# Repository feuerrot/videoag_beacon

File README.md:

# VideoAG Projekt: Beacon

Hardware ist an unbekannten Orten. Aber für die Aufnahme von Vorlesungen wüssten wir gerne, welche Hardware sich wo befindet. Die Lösung: Ein Beacon.
Auf der Basis eines nRF24L01+ und eines AVR wird so ein preiswertes und stromsparendes Stück Hardware implementiert, die sich jeweils am Equipment befindet und in regelmäßigen Intervallen eine eindeutige ID aussendet. Diese ID wird dann von einem dauerhaft lauschenden Empfänger verarbeitet.

## Projektstatus
Es existiert eine weitgehend stabile und laut Datenblätter stromsparende Idee für die Beacons. Platinen wurden designed und geätzt.

## Todo
* Platinen bestücken
* Firmware entwickeln
* Hardware testen
* Hardware für die Station designen

## Schaltplan und Layout

### Schaltplan

### Layout

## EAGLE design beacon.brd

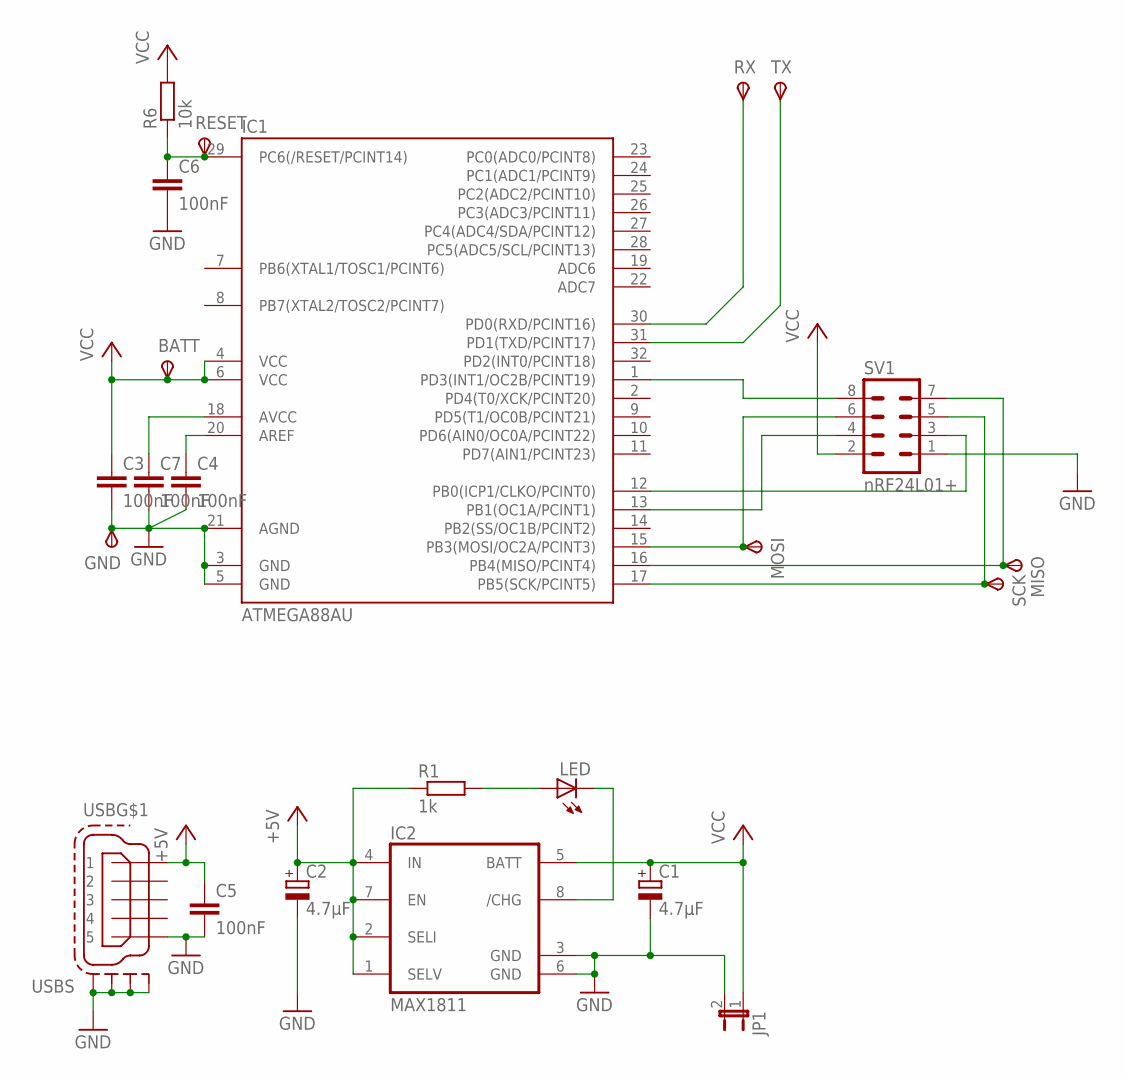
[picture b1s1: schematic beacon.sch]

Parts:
BATT: TPSB1,27; B1,27
C1, C2: 4.7μF; SMC_C
C3, C4, C5, C6, C7: 100nF; C0805
GND: TPSB1,27; B1,27
IC1: ATMEGA88AU; TQFP32-08
IC2: MAX1811; SO08
JP1: JP1E; JP1
LED: LEDCHIPLED_0805; CHIPLED_0805
MISO: TPSB1,27; B1,27
MOSI: TPSB1,27; B1,27
R1: 1k; M0805
R6: 10k; M0805
RESET: TPSB1,27; B1,27
RX: TPSB1,27; B1,27
SCK: TPSB1,27; B1,27
SV1: nRF24L01+; MA04-2
TX: TPSB1,27; B1,27
USB: MINI-USB-SCHIELD-32005-301; 32005-301

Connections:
+5V: C2.+, C5.1, IC2.1 (SELV), IC2.2 (SELI), IC2.4 (IN), IC2.7 (EN), R1.1, USB.1
AREF: C4.1, IC1.20 (AREF)
AVCC: C7.1, IC1.18 (AVCC)
GND: C1.-, C2.-, C3.2, C4.2, C5.2, C6.2, C7.2, GND.TP, IC1.3 (GND), IC1.5 (GND), IC1.21 (AGND), IC2.3 (GND), IC2.6 (GND), JP1.2, SV1.1, USB.5, USB.M1 (S1), USB.M2 (S2), USB.M3 (S3), USB.M4 (S4)
INT1: IC1.1 (PD3(INT1/OC2B/PCINT19)), SV1.8
MISO: IC1.16 (PB4(MISO/PCINT4)), MISO.TP, SV1.7
MOSI: IC1.15 (PB3(MOSI/OC2A/PCINT3)), MOSI.TP, SV1.6
unnamed: LED.A, R1.2
unnamed: IC2.8 (/CHG), LED.C
PB0: IC1.12 (PB0(ICP1/CLKO/PCINT0)), SV1.3
PB1: IC1.13 (PB1(OC1A/PCINT1)), SV1.4
RESET: C6.1, IC1.29 (PC6(/RESET/PCINT14)), R6.1, RESET.TP
RX: IC1.30 (PD0(RXD/PCINT16)), RX.TP
SCK: IC1.17 (PB5(SCK/PCINT5)), SCK.TP, SV1.5
TX: IC1.31 (PD1(TXD/PCINT17)), TX.TP
VCC: BATT.TP, C1.+, C3.1, IC1.4 (VCC), IC1.6 (VCC), IC2.5 (BATT), JP1.1, R6.2, SV1.2

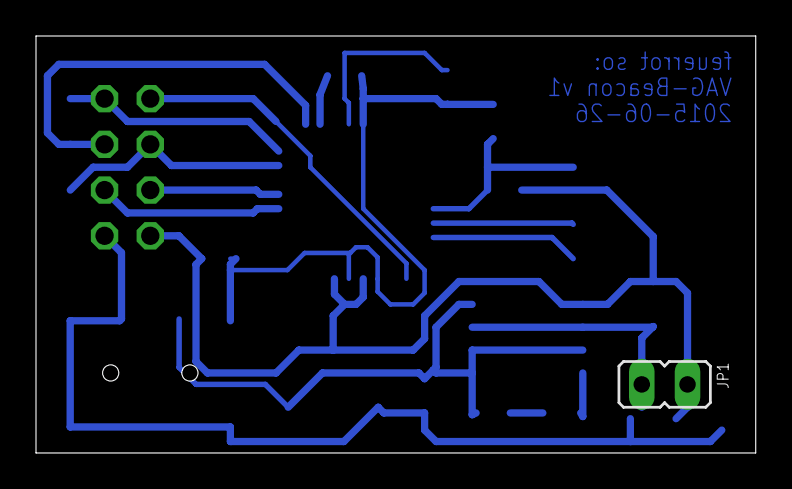
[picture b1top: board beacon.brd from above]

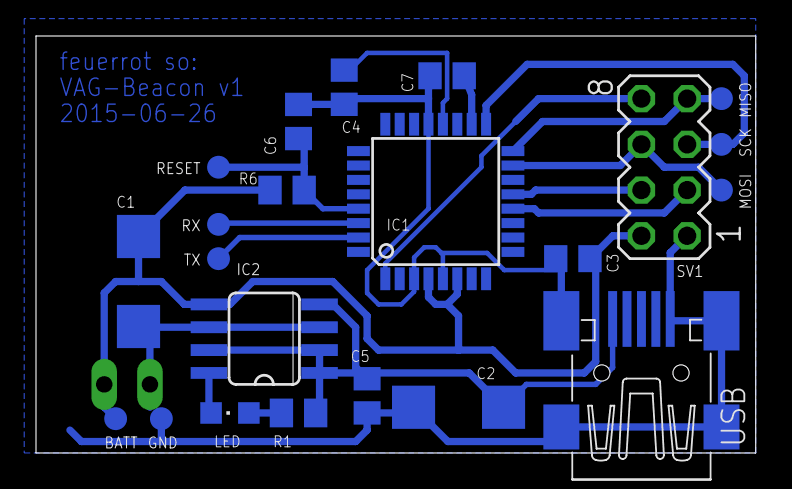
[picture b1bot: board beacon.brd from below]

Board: 2 copper layers, 40.0 x 23.2 mm, 23 parts (22 on the bottom side), 16 nets.

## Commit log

2015-06-26 README.md: add readme
2015-06-26 add readme-images
2015-06-26 update name+value
2015-06-26 add image of layout
2015-06-26 fix board image
2015-06-26 src/: add source skeleton
2015-07-16 Readme.md: Todoliste
